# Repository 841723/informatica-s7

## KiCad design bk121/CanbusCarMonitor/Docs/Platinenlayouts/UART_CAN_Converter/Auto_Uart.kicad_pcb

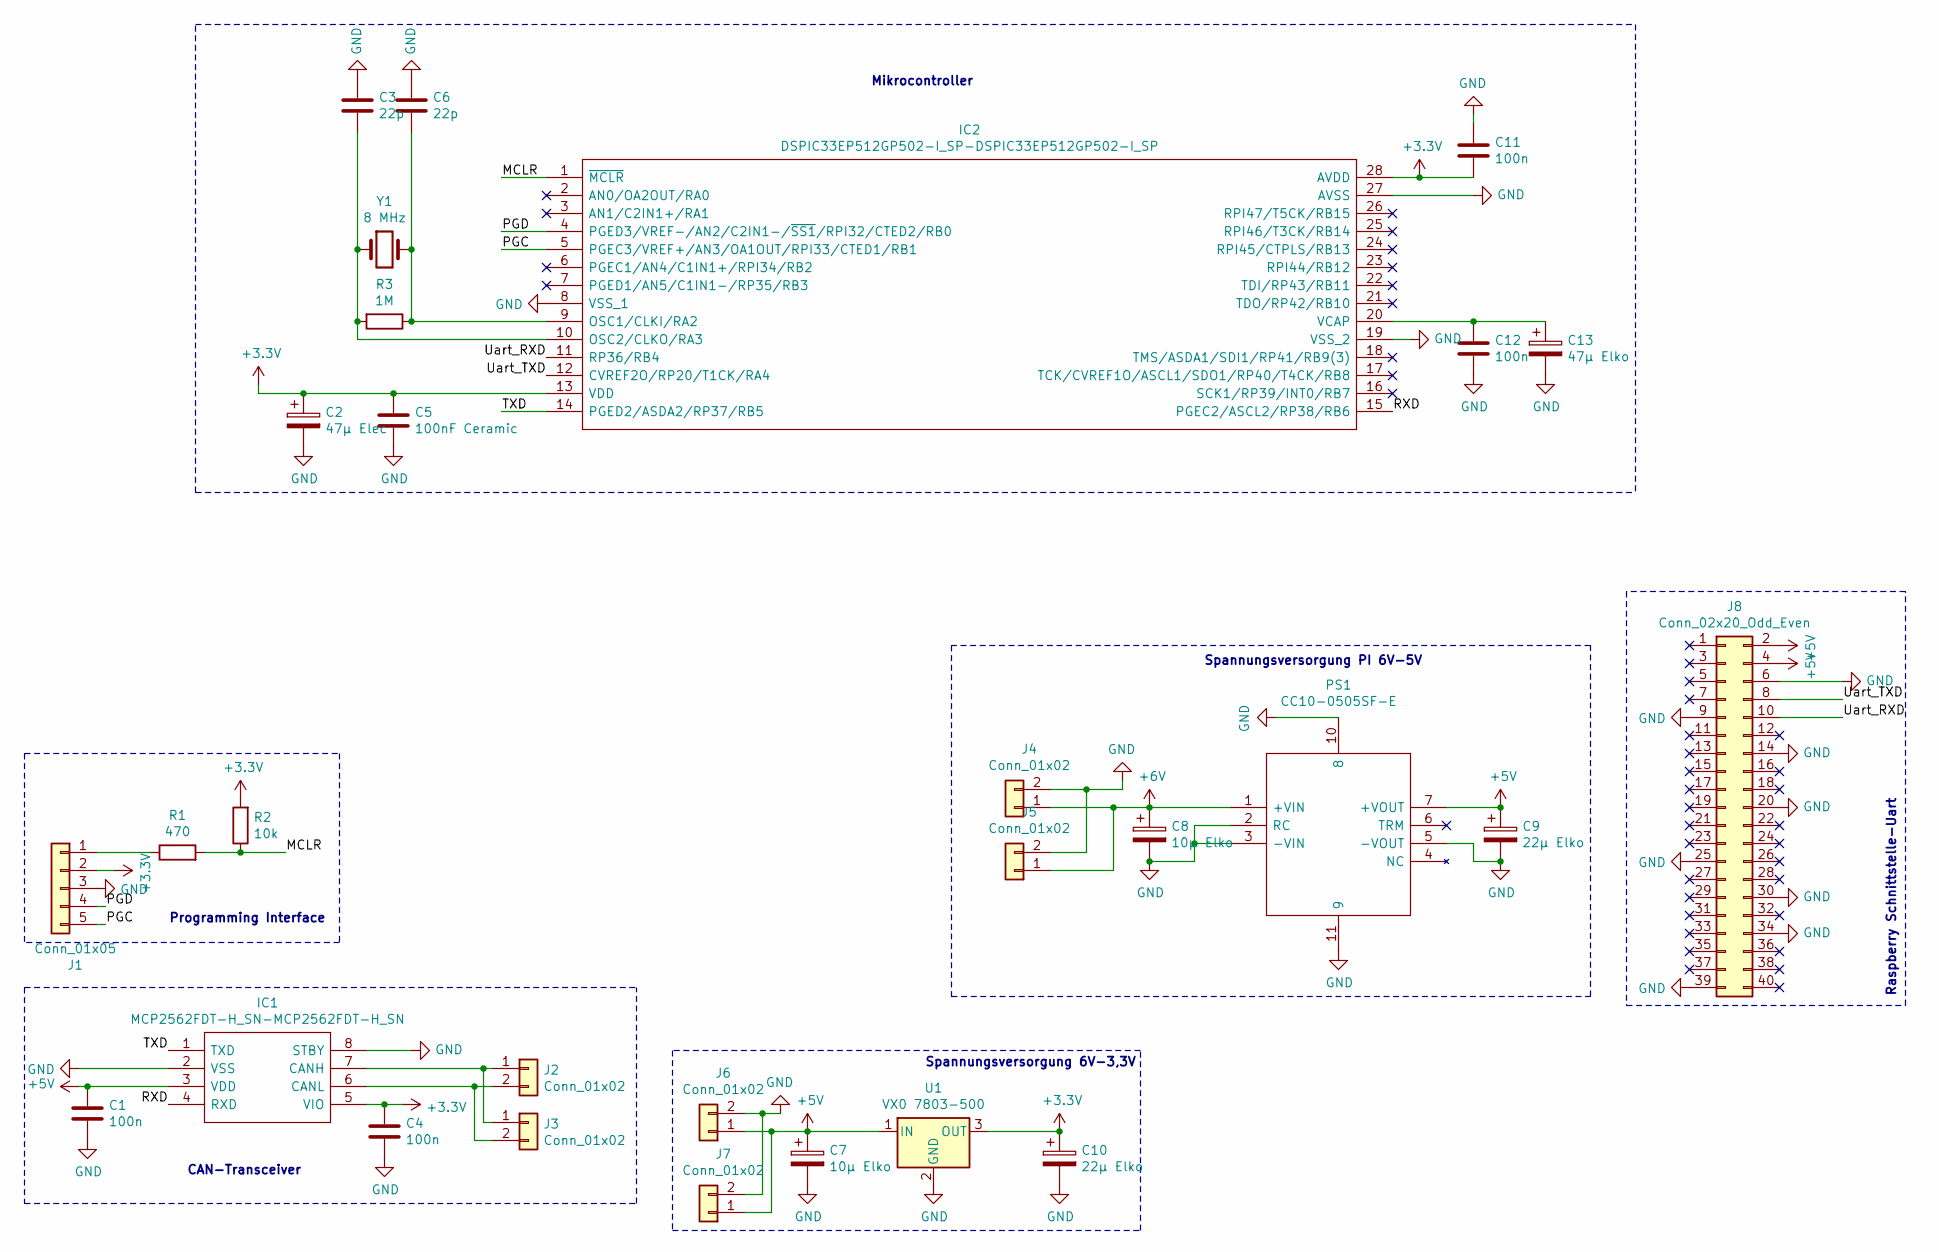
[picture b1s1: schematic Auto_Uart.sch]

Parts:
C1, C4, C11, C12: 100n; C_0805_2012Metric_Pad1.18x1.45mm_HandSolder
C2: 47µ Elec; CP_Elec_5x5.4
C3, C6: 22p; C_0805_2012Metric_Pad1.18x1.45mm_HandSolder
C5: 100nF Ceramic; C_0805_2012Metric_Pad1.18x1.45mm_HandSolder
C7, C8: 10µ Elko; CP_Elec_4x4.5
C9, C10: 22µ Elko; CP_Elec_4x4.5
C13: 47µ Elko; CP_Elec_5x5.4
IC1: MCP2562FDT-H_SN-MCP2562FDT-H_SN; DIP-8_W7.62mm_Socket_LongPads; Mouser Part Number 579-MCP2562FDT-H/SN
IC2: DSPIC33EP512GP502-I_SP-DSPIC33EP512GP502-I_SP; DIP-28_W7.62mm_Socket_LongPads; Mouser Part Number 579-33EP512GP502ISP
J1: Conn_01x05; PinHeader_1x05_P2.54mm_Vertical
J2, J3: Conn_01x02; Molex_KK-254_AE-6410-02A_1x02_P2.54mm_Vertical
J4, J5, J6, J7: Conn_01x02; TerminalBlock_Phoenix_MKDS-3-2-5.08_1x02_P5.08mm_Horizontal
J8: Conn_02x20_Odd_Even; PinSocket_2x20_P2.54mm_Vertical
PS1: CC10-0505SF-E; CC100505SFE; Manufacturer_Part_Number CC10-0505SF-E
R1: 470; R_0805_2012Metric_Pad1.20x1.40mm_HandSolder
R2: 10k; R_0805_2012Metric_Pad1.20x1.40mm_HandSolder
R3: 1M; R_0805_2012Metric_Pad1.20x1.40mm_HandSolder
U1: VX0 7803-500; Converter_DCDC_RECOM_R-78E-0.5_THT
Y1: 8 MHz; Crystal_HC49-4H_Vertical

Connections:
+3V3: C2.1, C4.1, C5.1, C10.1, C11.2, IC1.5 (VIO), IC2.13 (VDD), IC2.28 (AVDD), J1.2, R2.2, U1.3 (OUT)
+5V: C1.1, C7.1, C9.1, IC1.3 (VDD), J6.1, J7.1, J8.2, J8.4, PS1.7 (+VOUT), U1.1 (IN)
+6V: C8.1, J4.1, J5.1, PS1.1 (+VIN)
/MCLR: IC2.1 (~MCLR), R1.2, R2.1
/PGC: IC2.5 (PGEC3/VREF+/AN3/OA1OUT/RPI33/CTED1/RB1), J1.5
/PGD: IC2.4 (PGED3/VREF-/AN2/C2IN1-/~SS1~/RPI32/CTED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), J1.4
/RXD: IC1.4 (RXD), IC2.15 (PGEC2/ASCL2/RP38/RB6)
/TXD: IC1.1 (TXD), IC2.14 (PGED2/ASDA2/RP37/RB5)
/Uart_RXD: IC2.11 (RP36/RB4), J8.10
/Uart_TXD: IC2.12 (CVREF2O/RP20/T1CK/RA4), J8.8
GND: C1.2, C2.2, C3.1, C4.2, C5.2, C6.2, C7.2, C8.2, C9.2, C10.2, C11.1, C12.2, C13.2, IC1.2 (VSS), IC1.8 (STBY), IC2.8 (VSS_1), IC2.19 (VSS_2), IC2.27 (AVSS), J1.3, J4.2, J5.2, J6.2, J7.2, J8.6, J8.9, J8.14, J8.20, J8.25, J8.30, J8.34, J8.39, PS1.2 (RC), PS1.3 (-VIN), PS1.5 (-VOUT), PS1.10 (8), PS1.11 (9), U1.2 (GND)
unnamed: C3.2, IC2.10 (OSC2/CLKO/RA3), R3.2, Y1.1
unnamed: C6.1, IC2.9 (OSC1/CLKI/RA2), R3.1, Y1.2
unnamed: C12.1, C13.1, IC2.20 (VCAP)
unnamed: IC1.6 (CANL), J2.2, J3.2
unnamed: IC1.7 (CANH), J2.1, J3.1
unnamed: J1.1, R1.1

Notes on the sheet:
Mikrocontroller
Programming Interface
CAN-Transceiver
Raspberry Schnittstelle-Uart
Spannungsversorgung 6V-3,3V
Spannungsversorgung PI 6V-5V

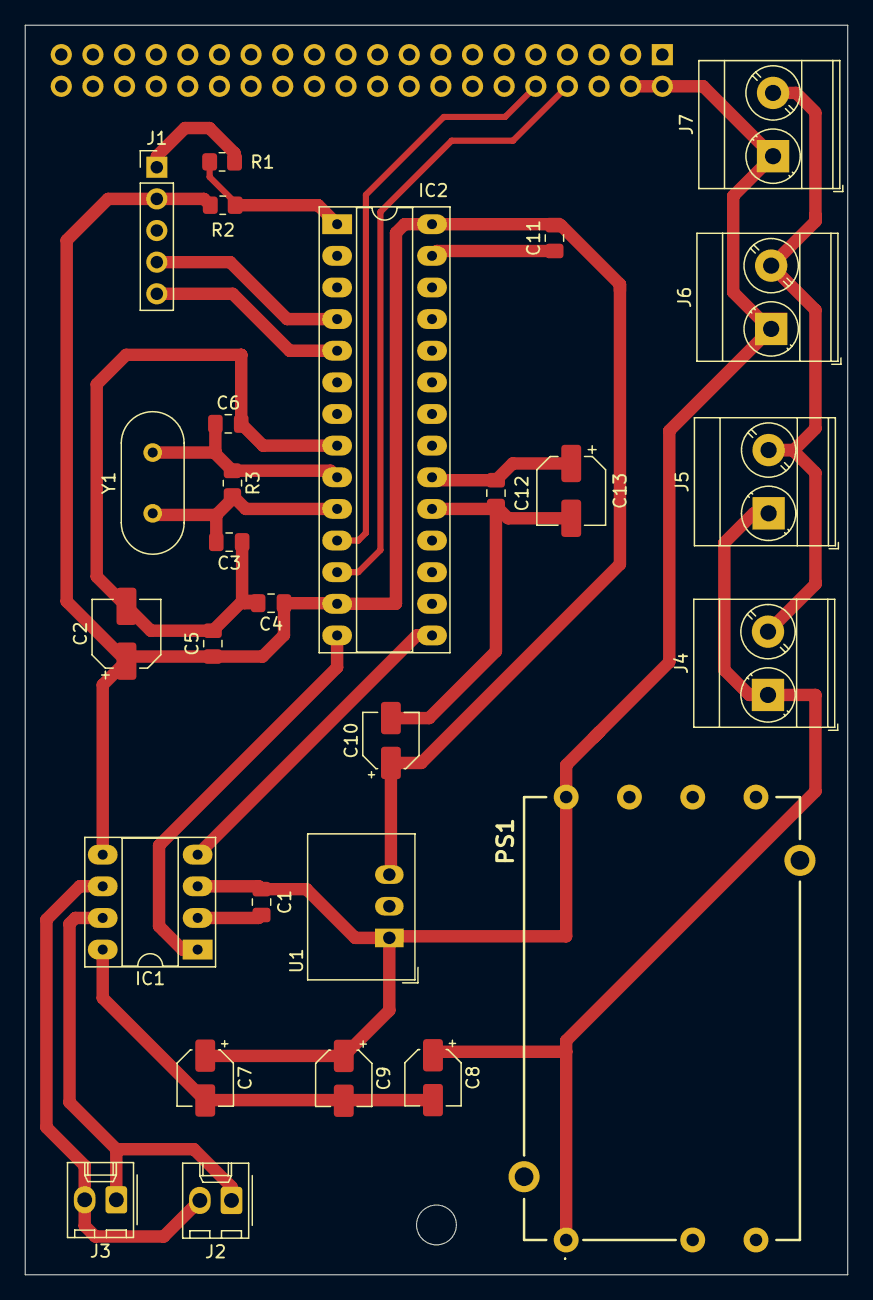
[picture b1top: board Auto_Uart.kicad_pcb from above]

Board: 2 copper layers, 66.0 x 100.3 mm, 29 parts (1 on the bottom side), 17 nets.

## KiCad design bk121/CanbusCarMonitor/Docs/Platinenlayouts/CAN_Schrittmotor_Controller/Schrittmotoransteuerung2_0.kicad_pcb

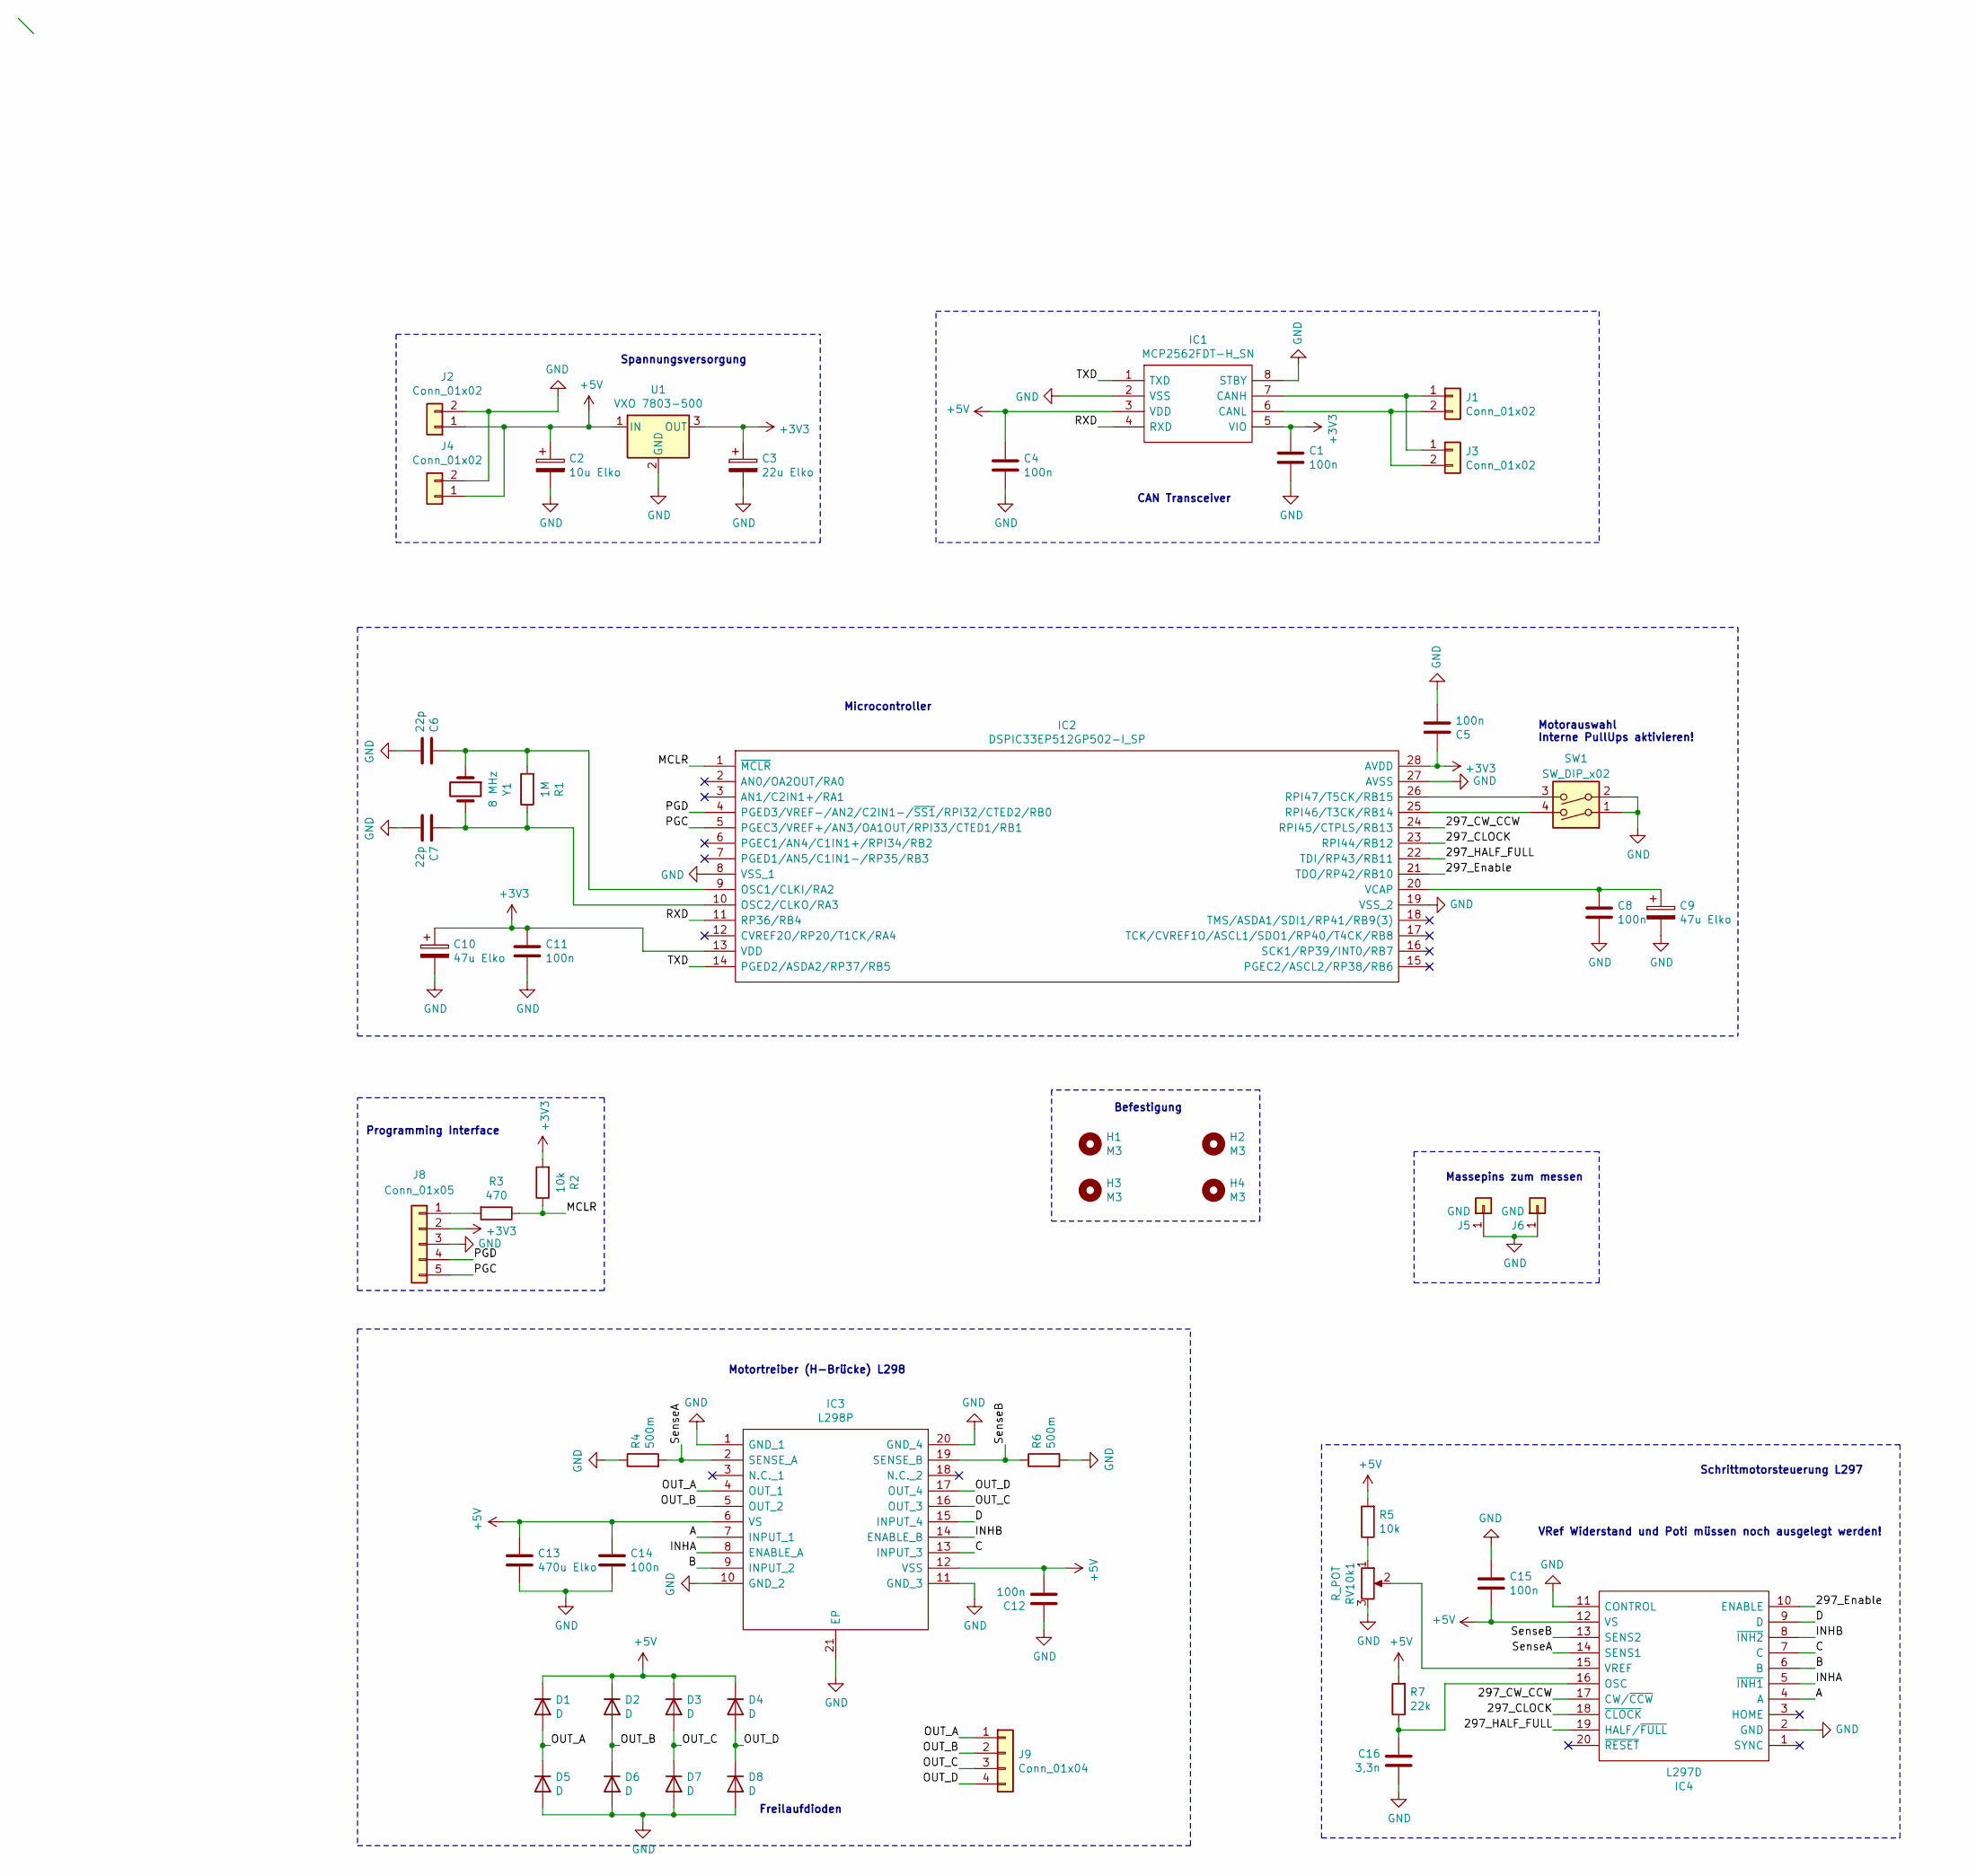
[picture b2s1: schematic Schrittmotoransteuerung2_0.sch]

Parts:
C1, C4, C5, C8, C11, C12, C14, C15: 100n; C_0805_2012Metric_Pad1.18x1.45mm_HandSolder
C2: 10u Elko; CP_Elec_4x4.5
C3: 22u Elko; CP_Elec_4x4.5
C6, C7: 22p; C_0805_2012Metric_Pad1.18x1.45mm_HandSolder
C9, C10: 47u Elko; CP_Elec_5x5.4
C13: 470u Elko; CP_Elec_10x10.5
C16: 3,3n; C_0805_2012Metric_Pad1.18x1.45mm_HandSolder
D1, D2, D3, D4, D5, D6, D7, D8: D; D_SMB_Handsoldering
H1, H2, H3, H4: M3; MountingHole_3.2mm_M3
IC1: MCP2562FDT-H_SN; DIP-8_W7.62mm_Socket_LongPads; Mouser Part Number 579-MCP2562FDT-H/SN
IC2: DSPIC33EP512GP502-I_SP; DIP-28_W7.62mm_Socket_LongPads; Mouser Part Number 579-33EP512GP502ISP
IC3: L298P; HSOP-20-1EP_11.0x15.9mm_P1.27mm_SlugDown_ThermalVias; Mouser Part Number 511-L298P
IC4: L297D; SOIC127P1032X265-20N; Mouser Part Number 511-L297D
J1, J3: Conn_01x02; Molex_KK-254_AE-6410-02A_1x02_P2.54mm_Vertical
J2, J4: Conn_01x02; TerminalBlock_Phoenix_MKDS-3-2-5.08_1x02_P5.08mm_Horizontal
J5, J6: GND; PinHeader_1x01_P2.54mm_Vertical
J8: Conn_01x05; PinHeader_1x05_P2.54mm_Vertical
J9: Conn_01x04; TerminalBlock_Phoenix_MKDS-3-4-5.08_1x04_P5.08mm_Horizontal
R1: 1M; R_0805_2012Metric_Pad1.20x1.40mm_HandSolder
R2, R5: 10k; R_0805_2012Metric_Pad1.20x1.40mm_HandSolder
R3: 470; R_0805_2012Metric_Pad1.20x1.40mm_HandSolder
R4, R6: 500m; R_2512_6332Metric_Pad1.40x3.35mm_HandSolder
R7: 22k; R_0805_2012Metric_Pad1.20x1.40mm_HandSolder
RV10k1: R_POT; Potentiometer_Bourns_3296W_Vertical
SW1: SW_DIP_x02; SW_DIP_SPSTx02_Piano_10.8x6.64mm_W7.62mm_P2.54mm
U1: VXO 7803-500; Converter_DCDC_RECOM_R-78E-0.5_THT
Y1: 8 MHz; Crystal_HC49-4H_Vertical

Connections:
+3V3: C1.1, C3.1, C5.1, C10.1, C11.1, IC1.5 (VIO), IC2.13 (VDD), IC2.28 (AVDD), J8.2, R2.2, U1.3 (OUT)
+5V: C2.1, C4.1, C12.2, C13.1, C14.1, C15.2, D1.1 (K), D2.1 (K), D3.1 (K), D4.1 (K), IC1.3 (VDD), IC3.6 (VS), IC3.12 (VSS), IC4.12 (VS), J2.1, J4.1, R5.2, R7.2, U1.1 (IN)
/297_CLOCK: IC2.23 (RPI44/RB12), IC4.18 (~CLOCK)
/297_CW_CCW: IC2.24 (RPI45/CTPLS/RB13), IC4.17 (CW/~CCW)
/297_Enable: IC2.21 (TDO/RP42/RB10), IC4.10 (ENABLE)
/297_HALF_FULL: IC2.22 (TDI/RP43/RB11), IC4.19 (HALF/~FULL)
/A: IC3.7 (INPUT_1), IC4.4 (A)
/B: IC3.9 (INPUT_2), IC4.6 (B)
/C: IC3.13 (INPUT_3), IC4.7 (C)
/D: IC3.15 (INPUT_4), IC4.9 (D)
/INHA: IC3.8 (ENABLE_A), IC4.5 (~INH1)
/INHB: IC3.14 (ENABLE_B), IC4.8 (~INH2)
/MCLR: IC2.1 (~MCLR), R2.1, R3.1
/OUT_A: D1.2 (A), D5.1 (K), IC3.4 (OUT_1), J9.1
/OUT_B: D2.2 (A), D6.1 (K), IC3.5 (OUT_2), J9.2
/OUT_C: D3.2 (A), D7.1 (K), IC3.16 (OUT_3), J9.3
/OUT_D: D4.2 (A), D8.1 (K), IC3.17 (OUT_4), J9.4
/PGC: IC2.5 (PGEC3/VREF+/AN3/OA1OUT/RPI33/CTED1/RB1), J8.5
/PGD: IC2.4 (PGED3/VREF-/AN2/C2IN1-/~SS1~/RPI32/CTED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), J8.4
/RXD: IC1.4 (RXD), IC2.11 (RP36/RB4)
/SenseA: IC3.2 (SENSE_A), IC4.14 (SENS1), R4.2
/SenseB: IC3.19 (SENSE_B), IC4.13 (SENS2), R6.1
/TXD: IC1.1 (TXD), IC2.14 (PGED2/ASDA2/RP37/RB5)
GND: C1.2, C2.2, C3.2, C4.2, C5.2, C6.2, C7.2, C8.2, C9.2, C10.2, C11.2, C12.1, C13.2, C14.2, C15.1, C16.2, D5.2 (A), D6.2 (A), D7.2 (A), D8.2 (A), IC1.2 (VSS), IC1.8 (STBY), IC2.8 (VSS_1), IC2.19 (VSS_2), IC2.27 (AVSS), IC3.1 (GND_1), IC3.10 (GND_2), IC3.11 (GND_3), IC3.20 (GND_4), IC3.21 (EP), IC4.2 (GND), IC4.11 (CONTROL), J2.2, J4.2, J5.1, J6.1, J8.3, R4.1, R6.2, RV10k1.3, SW1.1, SW1.2, U1.2 (GND)
unnamed: C6.1, IC2.9 (OSC1/CLKI/RA2), R1.2, Y1.1
unnamed: C7.1, IC2.10 (OSC2/CLKO/RA3), R1.1, Y1.2
unnamed: C8.1, C9.1, IC2.20 (VCAP)
unnamed: C16.1, IC4.16 (OSC), R7.1
unnamed: IC1.6 (CANL), J1.2, J3.2
unnamed: IC1.7 (CANH), J1.1, J3.1
unnamed: IC2.25 (RPI46/T3CK/RB14), SW1.4
unnamed: IC2.26 (RPI47/T5CK/RB15), SW1.3
unnamed: IC4.15 (VREF), RV10k1.2
unnamed: J8.1, R3.2
unnamed: R5.1, RV10k1.1

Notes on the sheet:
Spannungsversorgung
Programming Interface
Microcontroller
CAN Transceiver
Schrittmotorsteuerung L297
VRef Widerstand und Poti müssen noch ausgelegt werden!
Motorauswahl Interne PullUps aktivieren!
Motortreiber (H-Brücke) L298
Freilaufdioden
Massepins zum messen
Befestigung

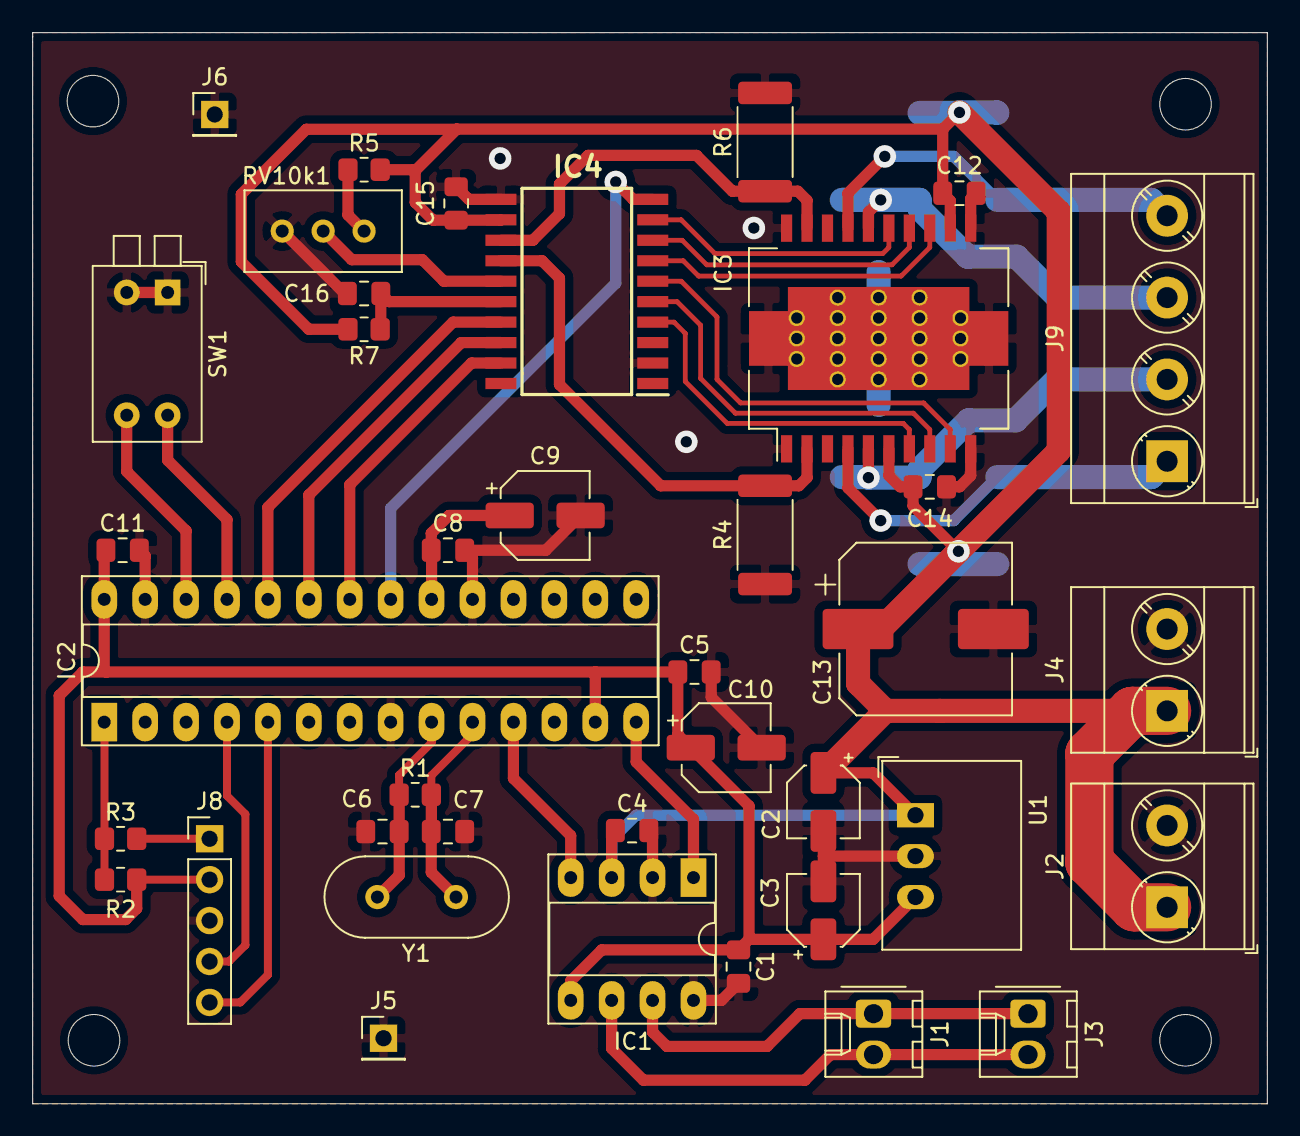
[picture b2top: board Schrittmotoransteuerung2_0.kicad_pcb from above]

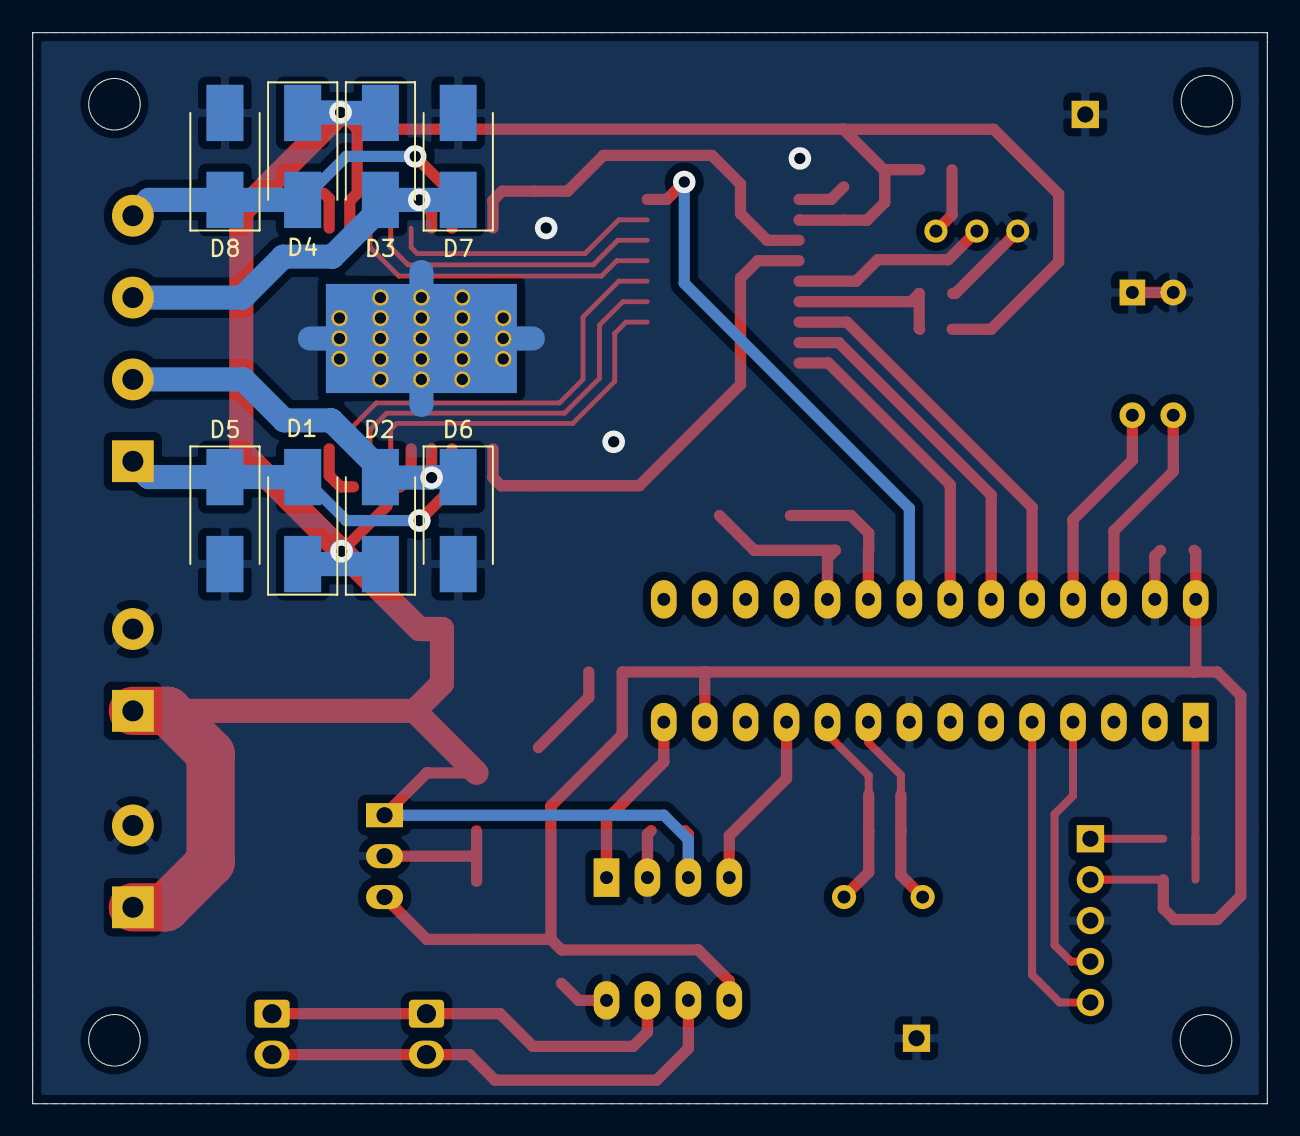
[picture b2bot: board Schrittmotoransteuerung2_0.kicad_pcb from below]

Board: 2 copper layers, 76.6 x 66.5 mm, 51 parts (8 on the bottom side), 35 nets.

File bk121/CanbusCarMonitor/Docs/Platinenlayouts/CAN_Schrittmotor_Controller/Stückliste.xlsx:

Reference | Quantity | 4x Quantity | Value | Footprint
C1 C4 C5 C8 C11 C12 C14 C15 | 8 | 32 | 100n | Capacitor_SMD:C_0805_2012Metric_Pad1.18x1.45mm_HandSolder
C13 | 1 | 4 | 470u Elko | Capacitor_SMD:CP_Elec_10x10.5
C16 | 1 | 4 | 3,3n | Capacitor_SMD:C_0805_2012Metric_Pad1.18x1.45mm_HandSolder
C2 | 1 | 4 | 10u Elko | Capacitor_SMD:CP_Elec_4x4.5
C3 | 1 | 4 | 22u Elko | Capacitor_SMD:CP_Elec_4x4.5
C6 C7 | 2 | 8 | 22p | Capacitor_SMD:C_0805_2012Metric_Pad1.18x1.45mm_HandSolder
C9 C10 | 2 | 8 | 47u Elko | Capacitor_SMD:CP_Elec_5x5.4
D1 D2 D3 D4 D5 D6 D7 D8 | 8 | 32 | D | Diode_SMD:D_SMB_Handsoldering
IC1 | 1 | 4 | MCP2562FDT-H_SN | Package_DIP:DIP-8_W7.62mm_Socket_LongPads
IC2 | 1 | 4 | DSPIC33EP512GP502-I_SP | Package_DIP:DIP-28_W7.62mm_Socket_LongPads
IC3 | 1 | 4 | L298P | L298:SOIC127P1420X360-21N
IC4 | 1 | 4 | L297D | L297:SOIC127P1032X265-20N
J1 J3 | 2 | 8 | Conn_01x02 | Connector_Molex:Molex_KK-254_AE-6410-02A_1x02_P2.54mm_Vertical
J2 J4 | 2 | 8 | Conn_01x02 | TerminalBlock_Phoenix_MKDS-3-2-5.08_1x02_P5.08mm_Horizontal
J5 J6 | 2 | 8 | GND | Connector_PinHeader_2.54mm:PinHeader_1x01_P2.54mm_Vertical
J8 | 1 | 4 | Conn_01x05 | Connector_PinHeader_2.54mm:PinHeader_1x05_P2.54mm_Vertical
J9 | 1 | 4 | Conn_01x04 | TerminalBlock_Phoenix_MKDS-3-4-5.08_1x04_P5.08mm_Horizontal
R1 | 1 | 4 | 1M | Resistor_SMD:R_0805_2012Metric_Pad1.20x1.40mm_HandSolder
R3 | 1 | 4 | 470 | Resistor_SMD:R_0805_2012Metric_Pad1.20x1.40mm_HandSolder
R4 R6 | 2 | 8 | 500m | Resistor_SMD:R_2512_6332Metric_Pad1.40x3.35mm_HandSolder
R2 R5 | 2 | 8 | 10k | Resistor_SMD:R_0805_2012Metric_Pad1.20x1.40mm_HandSolder
R7 | 1 | 4 | 22k | Resistor_SMD:R_0805_2012Metric_Pad1.20x1.40mm_HandSolder
RV10k1 | 1 | 4 | R_POT | Potentiometer_THT:Potentiometer_Bourns_3296W_Vertical
SW1 | 1 | 4 | SW_DIP_x02 | SW_DIP_SPSTx02_Piano_10.8x6.64mm_W7.62mm_P2.54mm
U1 | 1 | 4 | VXO 7803-500 | Converter_DCDC:Converter_DCDC_RECOM_R-78E-0.5_THT
Y1 | 1 | 4 | 8 MHz | Crystal:Crystal_HC49-4H_Vertical

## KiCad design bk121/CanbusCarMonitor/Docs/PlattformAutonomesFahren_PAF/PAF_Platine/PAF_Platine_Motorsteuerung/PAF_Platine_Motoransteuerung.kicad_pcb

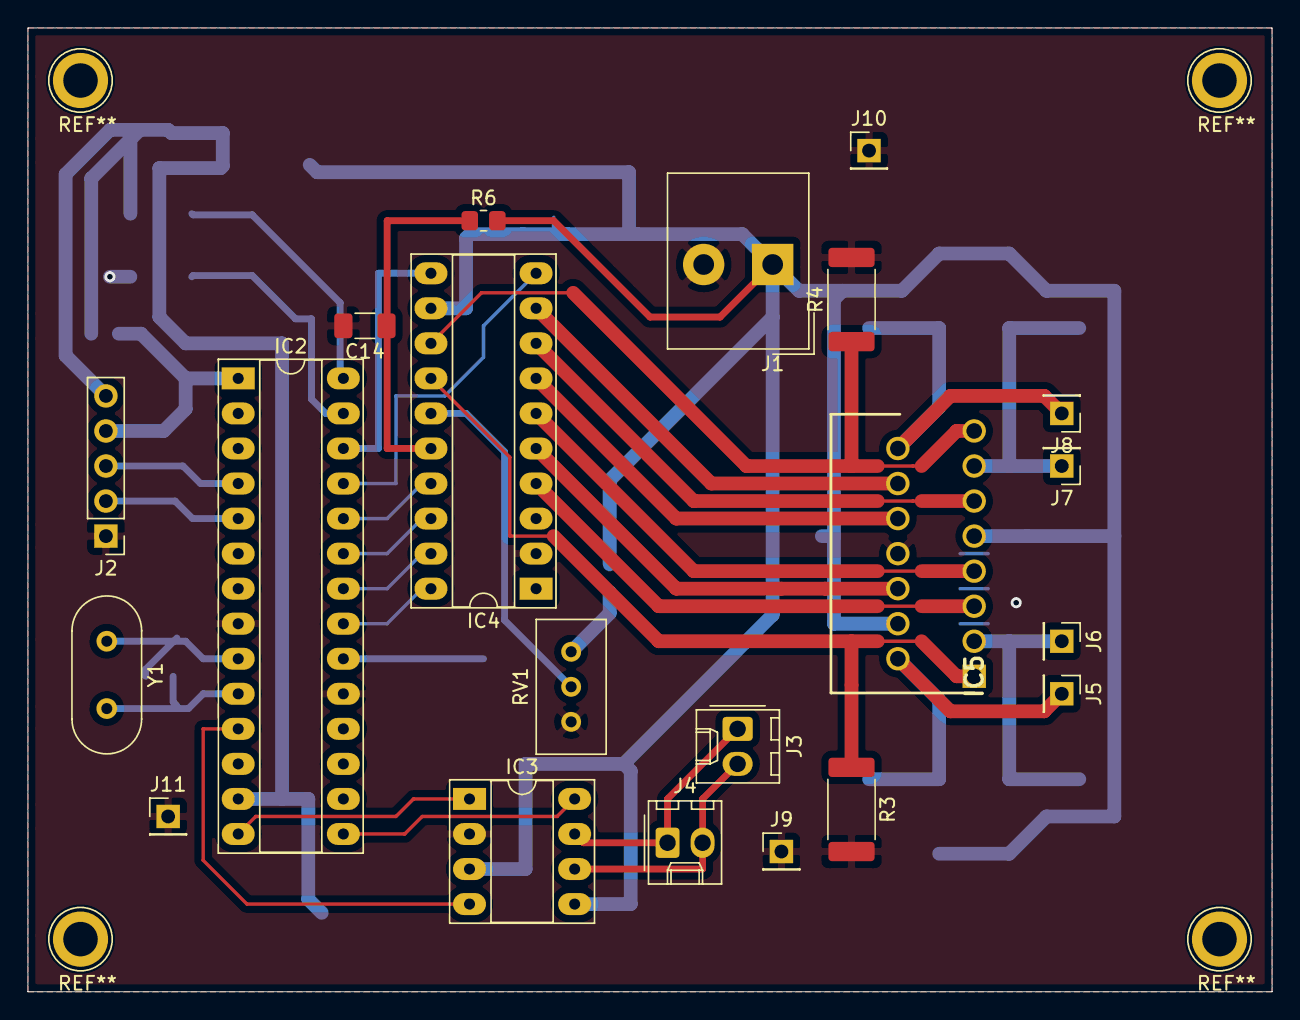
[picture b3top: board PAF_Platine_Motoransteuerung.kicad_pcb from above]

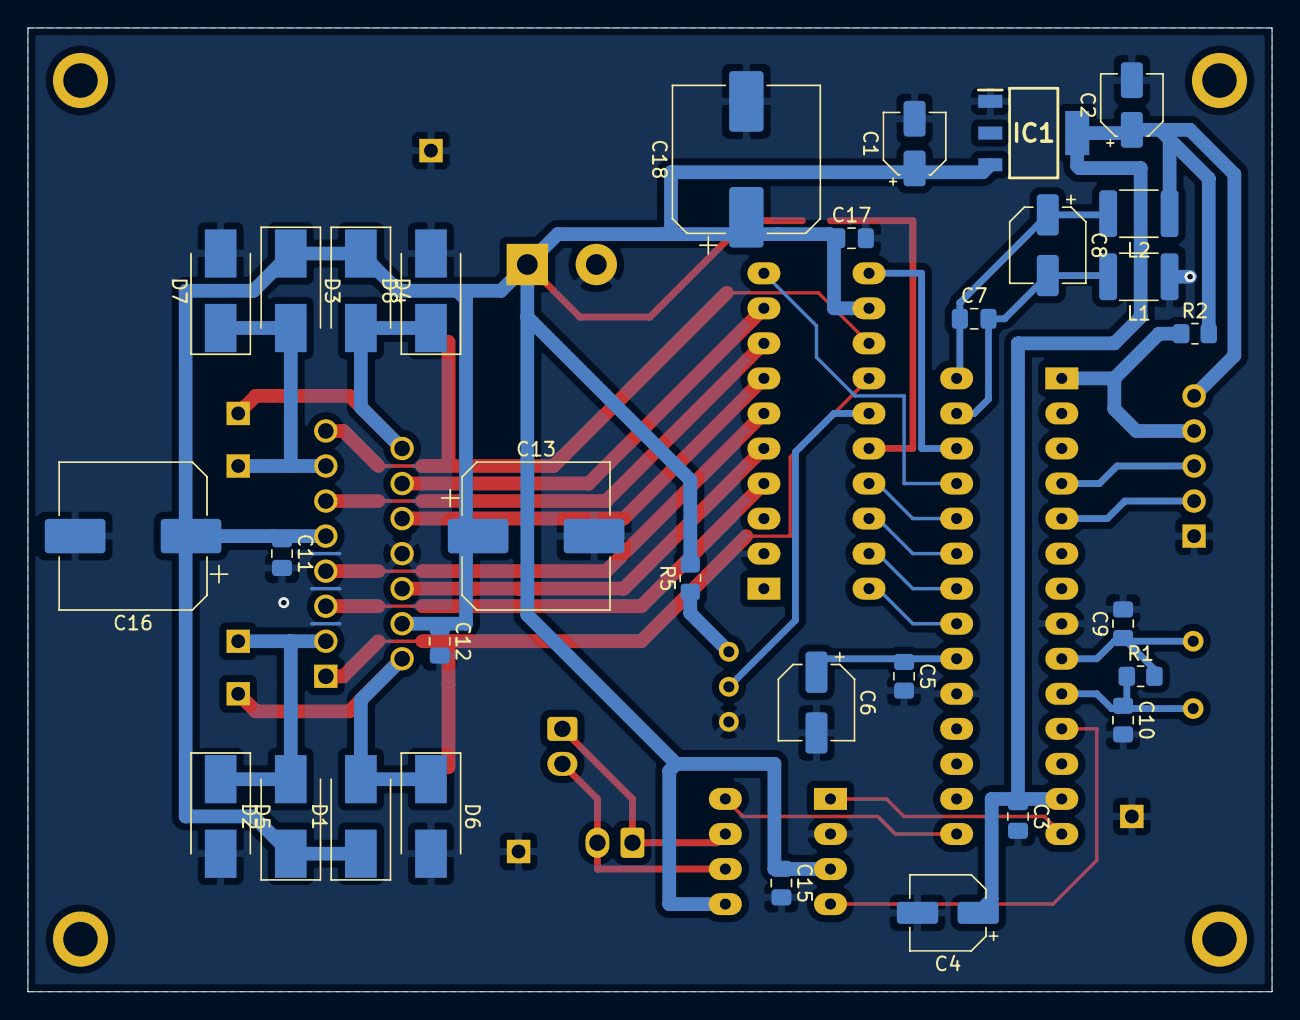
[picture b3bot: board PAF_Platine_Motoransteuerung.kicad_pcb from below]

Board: 2 copper layers, 90.2 x 69.9 mm, 52 parts (31 on the bottom side), 37 nets.

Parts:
C1, C2: 10μF Elektrolyt; CP_Elec_4x4.5
C3, C5, C7, C11, C12, C15, C17: 100nF Ceramic; C_0805_2012Metric_Pad1.18x1.45mm_HandSolder
C4, C6, C8: 47μF Elec; CP_Elec_5x5.4
C9: 22pF Ceramic; C_0805_2012Metric_Pad1.18x1.45mm_HandSolder
C10: 22pF; C_0805_2012Metric_Pad1.18x1.45mm_HandSolder
C13, C16, C18: 470μF Elec; CP_Elec_10x10.5
C14: 3,3nF Ceramic; C_1206_3216Metric_Pad1.33x1.80mm_HandSolder
D1, D2, D3, D4, D5, D6, D7, D8: D; D_SMB_Handsoldering
IC1: LM1117IMP-3.3_NOPB; SOT230P700X180-4N
IC2: DSPIC33EP512GP502-I_SP; DIP-28_W7.62mm_Socket_LongPads
IC3: MCP2562FDT-H_SN; DIP-8_W7.62mm_Socket_LongPads
IC4: L297_1; DIP-20_W7.62mm_Socket_LongPads
IC5: L298N; TO127P500X2020X2210-15P
J1: Screw_Terminal_01x02; Altech_AK300_1x02_P5.00mm_45-Degree
J2: Conn_01x05; PinHeader_1x05_P2.54mm_Vertical
J3, J4: Conn_01x02; Molex_KK-254_AE-6410-02A_1x02_P2.54mm_Vertical
J5: Output 1; PinHeader_1x01_P2.54mm_Vertical
J6: Output 2; PinHeader_1x01_P2.54mm_Vertical
J7: Output 3; PinHeader_1x01_P2.54mm_Vertical
J8: Output 4; PinHeader_1x01_P2.54mm_Vertical
J9, J10, J11: GND; PinHeader_1x01_P2.54mm_Vertical
L1, L2: 820μH; L_1812_4532Metric_Pad1.30x3.40mm_HandSolder
R1: 1MΩ; R_0805_2012Metric_Pad1.20x1.40mm_HandSolder
R2: 11kΩ; R_0805_2012Metric_Pad1.20x1.40mm_HandSolder
R3, R4: 500mΩ; R_2512_6332Metric_Pad1.40x3.35mm_HandSolder
R5: R; R_0805_2012Metric_Pad1.20x1.40mm_HandSolder
R6: 22kΩ; R_0805_2012Metric_Pad1.20x1.40mm_HandSolder
RV1: R_POT; Potentiometer_Bourns_3296W_Vertical
Y1: Crystal; Crystal_HC49-4H_Vertical

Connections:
+3V3: C2.1, C3.1, C4.1, IC1.4, IC2.13, J2.5, L2.1, R2.2
+5V: C1.1, C11.1, C12.1, C13.1, C15.1, C16.1, C17.1, C18.1, D1.1, D2.1, D3.1, D4.1, IC1.3, IC3.3, IC3.5, IC4.12, IC5.4, IC5.9, J1.1, R5.2, R6.2
GND: C1.2, C2.2, C3.2, C4.2, C5.2, C6.2, C9.2, C10.2, C11.2, C12.2, C13.2, C14.2, C15.2, C16.2, C17.2, C18.2, D5.2, D6.2, D7.2, D8.2, IC1.1, IC2.8, IC2.19, IC3.2, IC4.2, IC5.8, J1.2, J2.1, J9.1, J10.1, J11.1, L1.1, R3.2, R4.2, RV1.3
unnamed: C5.1, C6.1, IC2.20
unnamed: C7.1, C8.1, IC2.28, L2.2
unnamed: C7.2, C8.2, IC2.27, L1.2
unnamed: C9.1, IC2.9, R1.2, Y1.1
unnamed: C10.1, IC2.10, R1.1, Y1.2
unnamed: C14.1, IC4.16, R6.1
unnamed: D1.2, D6.1, IC5.2, J5.1
unnamed: D2.2, D5.1, IC5.3, J6.1
unnamed: D3.2, D7.1, IC5.13, J7.1
unnamed: D4.2, D8.1, IC5.14, J8.1
unnamed: IC2.1, J2.4, R2.1
unnamed: IC2.4, J2.3
unnamed: IC2.5, J2.2
unnamed: IC2.11, IC3.4
unnamed: IC2.14, IC3.1
unnamed: IC2.15, IC3.8
unnamed: IC2.21, IC4.20
unnamed: IC2.22, IC4.19
unnamed: IC2.23, IC4.18
unnamed: IC2.24, IC4.17
unnamed: IC2.25, IC4.10
unnamed: IC2.26, IC4.11
unnamed: IC3.6, J3.2, J4.2
unnamed: IC3.7, J3.1, J4.1
unnamed: IC4.4, IC5.5
unnamed: IC4.5, IC5.6
unnamed: IC4.6, IC5.7
unnamed: IC4.7, IC5.10
unnamed: IC4.8, IC5.11
unnamed: IC4.9, IC5.12
unnamed: IC4.13, IC5.15, R4.1
unnamed: IC4.14, IC5.1, R3.1
unnamed: IC4.15, RV1.2
unnamed: R5.1, RV1.1

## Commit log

2024-10-04 inital commit
2024-10-07 TPDS 2024/10/07
2024-10-08 task1 handled
2024-10-08 second version task1 tpds
2024-10-09 bk121 & tpds class
2024-10-13 third version project1 tpds
2024-10-14 NSS - rename task.md file
2024-10-16 BK121 - push before path hardcoding
2024-10-16 BK121 - after 16/10/2024 class
2024-10-19 BK121 - after class 16/10/2024
2024-10-19 NSS - half done task2 debian
2024-10-23 NSS - update tasks.md
2024-10-23 TPDS - after 23-10-2024 class
2024-10-23 BK121 - SdImages 23/10/2024
2024-10-28 NSS - tasks
2024-10-28 TPDS - project2 after italian class
2024-10-28 TPDS - project2 codigo acabado
2024-11-01 TPDS - finish project 2
2024-11-01 TPDS - add round
2024-11-01 TPDS - add zip file
2024-11-01 TPDS - update requirements.txt
2024-11-07 NSS - Add WireGuard VPN
2024-11-07 NSS - Add debian-PPTP setup and remove debian-OpenVPN setup.
2024-11-08 NSS - Remove repeated instructions
2024-11-08 DL - Remove DL
2024-11-08 NSS - First template for task 5
2024-11-12 NSS - add windows wireguard set up
2024-11-12 NSS - Add windows SSTP VPN set up
2024-11-12 ACA - Add all files from linux
2024-11-13 BK121 - Add LTDC and DMA2D
2024-11-13 BK121 - Add FMC
2024-11-14 BK121 - Update .metadata files
2024-11-14 TPDS - Download numpy and pandas docs
2024-11-18 TPDS - Exam preparation and final exam handled
2024-11-19 BK121 - Try read images
2024-11-20 BK121 - Hardcodeados muchos includes
2024-11-20 MWD - Start of angular app
2024-11-22 NSS - Add task 4 and 5
2024-11-22 BK121 - Add some tests and nothing works
2024-11-22 BK121 - Delete .metadata
2024-11-22 NSS - Delete moved files
2024-11-24 NSS - Add cheatsheet of lab tasks 2-5 check
2024-11-24 BK121 - Can write into and read from files
2024-11-24 BK121 - Can write and read from framebuffer
2024-11-24 BK121 - Pre rar yt instalation
2024-11-24 BK121 - Works on slider_show_end/slider_show_end/slid
2024-11-24 BK121 - Remove .metadata files
2024-11-25 NSS - Add formula interpreter & Angular in mwd/chat
2024-12-02 BK121 - Works with shake
2024-12-02 BK121 - Works with transparency fade
2024-12-02 BK121 - Buttons added (non working)
2024-12-02 BK121 - Works click to change image
2024-12-02 DAF_A1 - Add test unit 4
2024-12-02 DVVA - First project dataset exploration
2024-12-02 DVVA - Submited problemset1 v1
2024-12-02 MWD - Add final project v1
2024-12-02 MWD - Add final project client v1
2024-12-04 BK121 - Add show file info with BUTTON_TAMPER
2024-12-04 DAF_A1 - Add test unit 5
2024-12-13 DVVA - Problem set 2 handled v1
2024-12-13 DVVA - Final project first exploration
2024-12-13 DVVA - Add moodle class contents
